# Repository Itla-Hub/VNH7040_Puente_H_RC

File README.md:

# VNH7040_Puente_H_RC
Circuito de puente H con el integrado ST VNH7040, con conexiones del PCB castellated

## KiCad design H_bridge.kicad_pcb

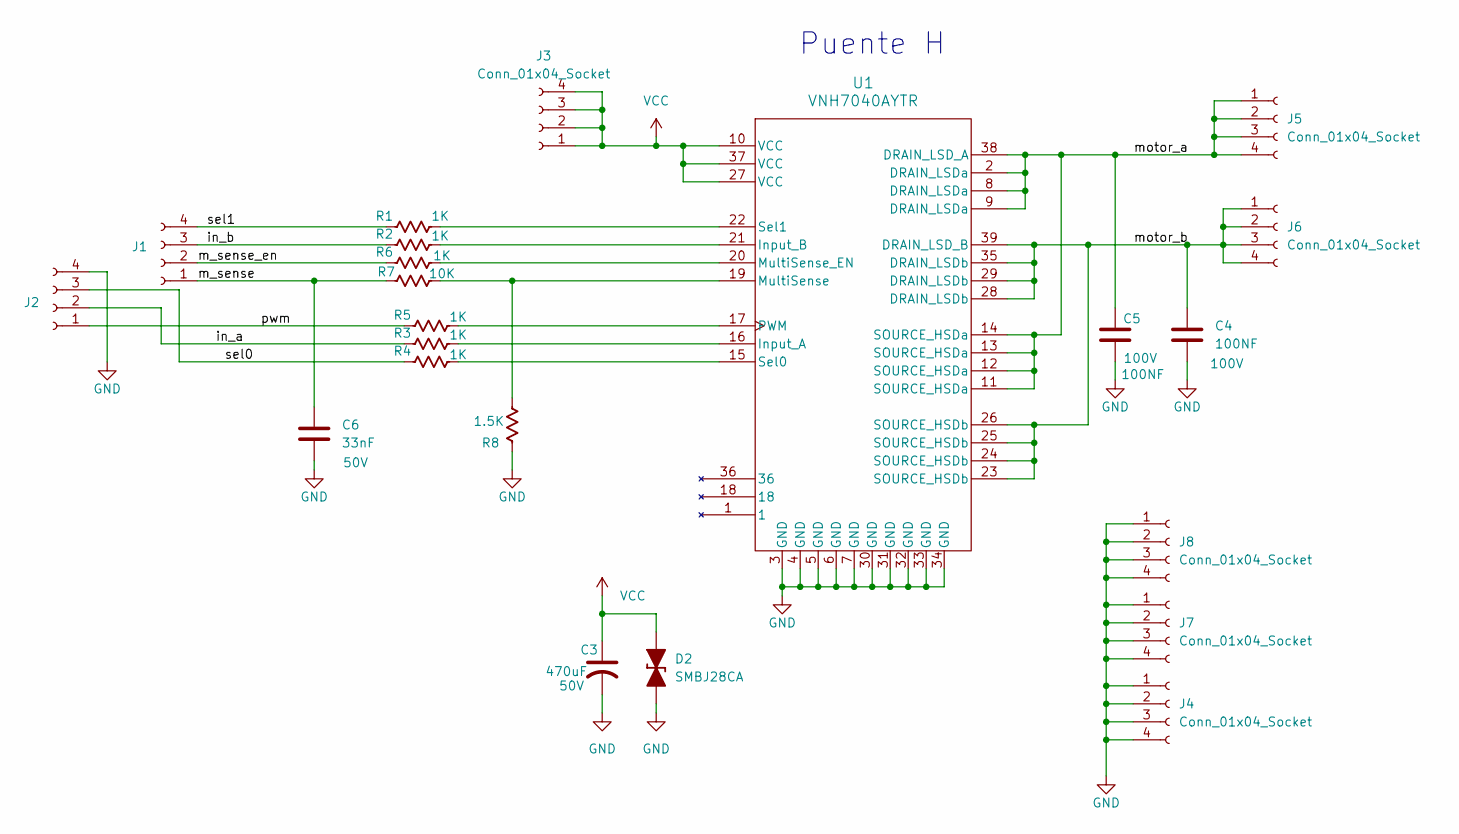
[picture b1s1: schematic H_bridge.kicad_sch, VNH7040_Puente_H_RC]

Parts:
C3: 470uF; CP_Elec_10x14.3; LCSC Part C22469994
C4, C5: 100NF; C_0805_2012Metric; LCSC Part C1853551
C6: 33nF; C_0603_1608Metric; LCSC Part C576851
D2: SMBJ28CA; D_SMB_TVS; LCSC Part C151259
J1, J2, J3, J4, J5, J6, J7, J8: Conn_01x04_Socket; PinSocket_1x04_P1.27mm_Castellated
R1, R2, R3, R4, R5, R6: 1K; R_0603_1608Metric; LCSC Part C22548
R7: 10K; R_0603_1608Metric; LCSC Part C98220
R8: 1.5K; R_0603_1608Metric; LCSC Part C114668
U1: VNH7040AYTR; POWERSSO-36TP_STM-M; LCSC Part C2969764

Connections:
/in_a: J2.2, R3.1
/in_b: J1.3, R2.1
/m_sense: C6.1, J1.1, R7.1
/m_sense_en: J1.2, R6.1
/motor_a: C5.1, J5.1, J5.2, J5.3, J5.4, U1.2 (DRAIN_LSDa), U1.8 (DRAIN_LSDa), U1.9 (DRAIN_LSDa), U1.11 (SOURCE_HSDa), U1.12 (SOURCE_HSDa), U1.13 (SOURCE_HSDa), U1.14 (SOURCE_HSDa), U1.38 (DRAIN_LSD_A)
/motor_b: C4.1, J6.1, J6.2, J6.3, J6.4, U1.23 (SOURCE_HSDb), U1.24 (SOURCE_HSDb), U1.25 (SOURCE_HSDb), U1.26 (SOURCE_HSDb), U1.28 (DRAIN_LSDb), U1.29 (DRAIN_LSDb), U1.35 (DRAIN_LSDb), U1.39 (DRAIN_LSD_B)
/pwm: J2.1, R5.1
/sel0: J2.3, R4.1
/sel1: J1.4, R1.1
GND: C3.2, C4.2, C5.2, C6.2, D2.1 (K), J2.4, J4.1, J4.2, J4.3, J4.4, J7.1, J7.2, J7.3, J7.4, J8.1, J8.2, J8.3, J8.4, R8.1, U1.3 (GND), U1.4 (GND), U1.5 (GND), U1.6 (GND), U1.7 (GND), U1.30 (GND), U1.31 (GND), U1.32 (GND), U1.33 (GND), U1.34 (GND)
unnamed: R3.2, U1.16 (Input_A)
unnamed: R2.2, U1.21 (Input_B)
unnamed: R7.2, R8.2, U1.19 (MultiSense)
unnamed: R6.2, U1.20 (MultiSense_EN)
unnamed: R5.2, U1.17 (PWM)
unnamed: R4.2, U1.15 (Sel0)
unnamed: R1.2, U1.22 (Sel1)
VCC: C3.1, D2.2 (A), J3.1, J3.2, J3.3, J3.4, U1.10 (VCC), U1.27 (VCC), U1.37 (VCC)

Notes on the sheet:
Puente H

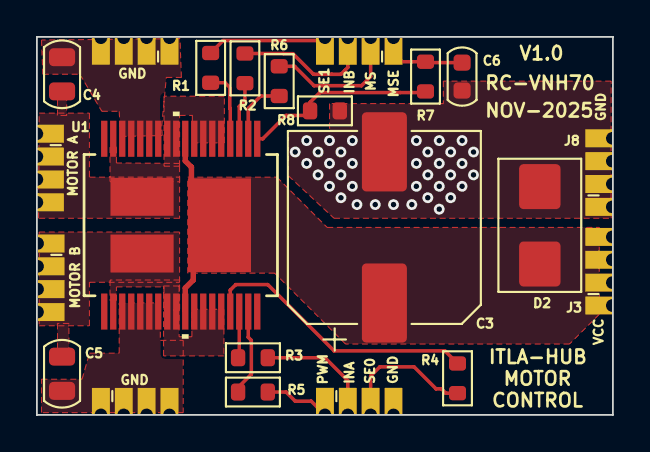
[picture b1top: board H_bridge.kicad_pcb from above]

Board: 2 copper layers, 32.0 x 21.0 mm, 22 parts (0 on the bottom side), 18 nets.

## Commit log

2025-11-16 Primera Version del circuito
2025-11-18 Primera version preliminar Conexiones y cobre completado Falta verificar las reglas y el BOM
2026-02-09 Actualizaciones de diseno genetrales.
2026-02-28 Completado el BOM
2026-03-01 Version 1 enviada a fabricacion
